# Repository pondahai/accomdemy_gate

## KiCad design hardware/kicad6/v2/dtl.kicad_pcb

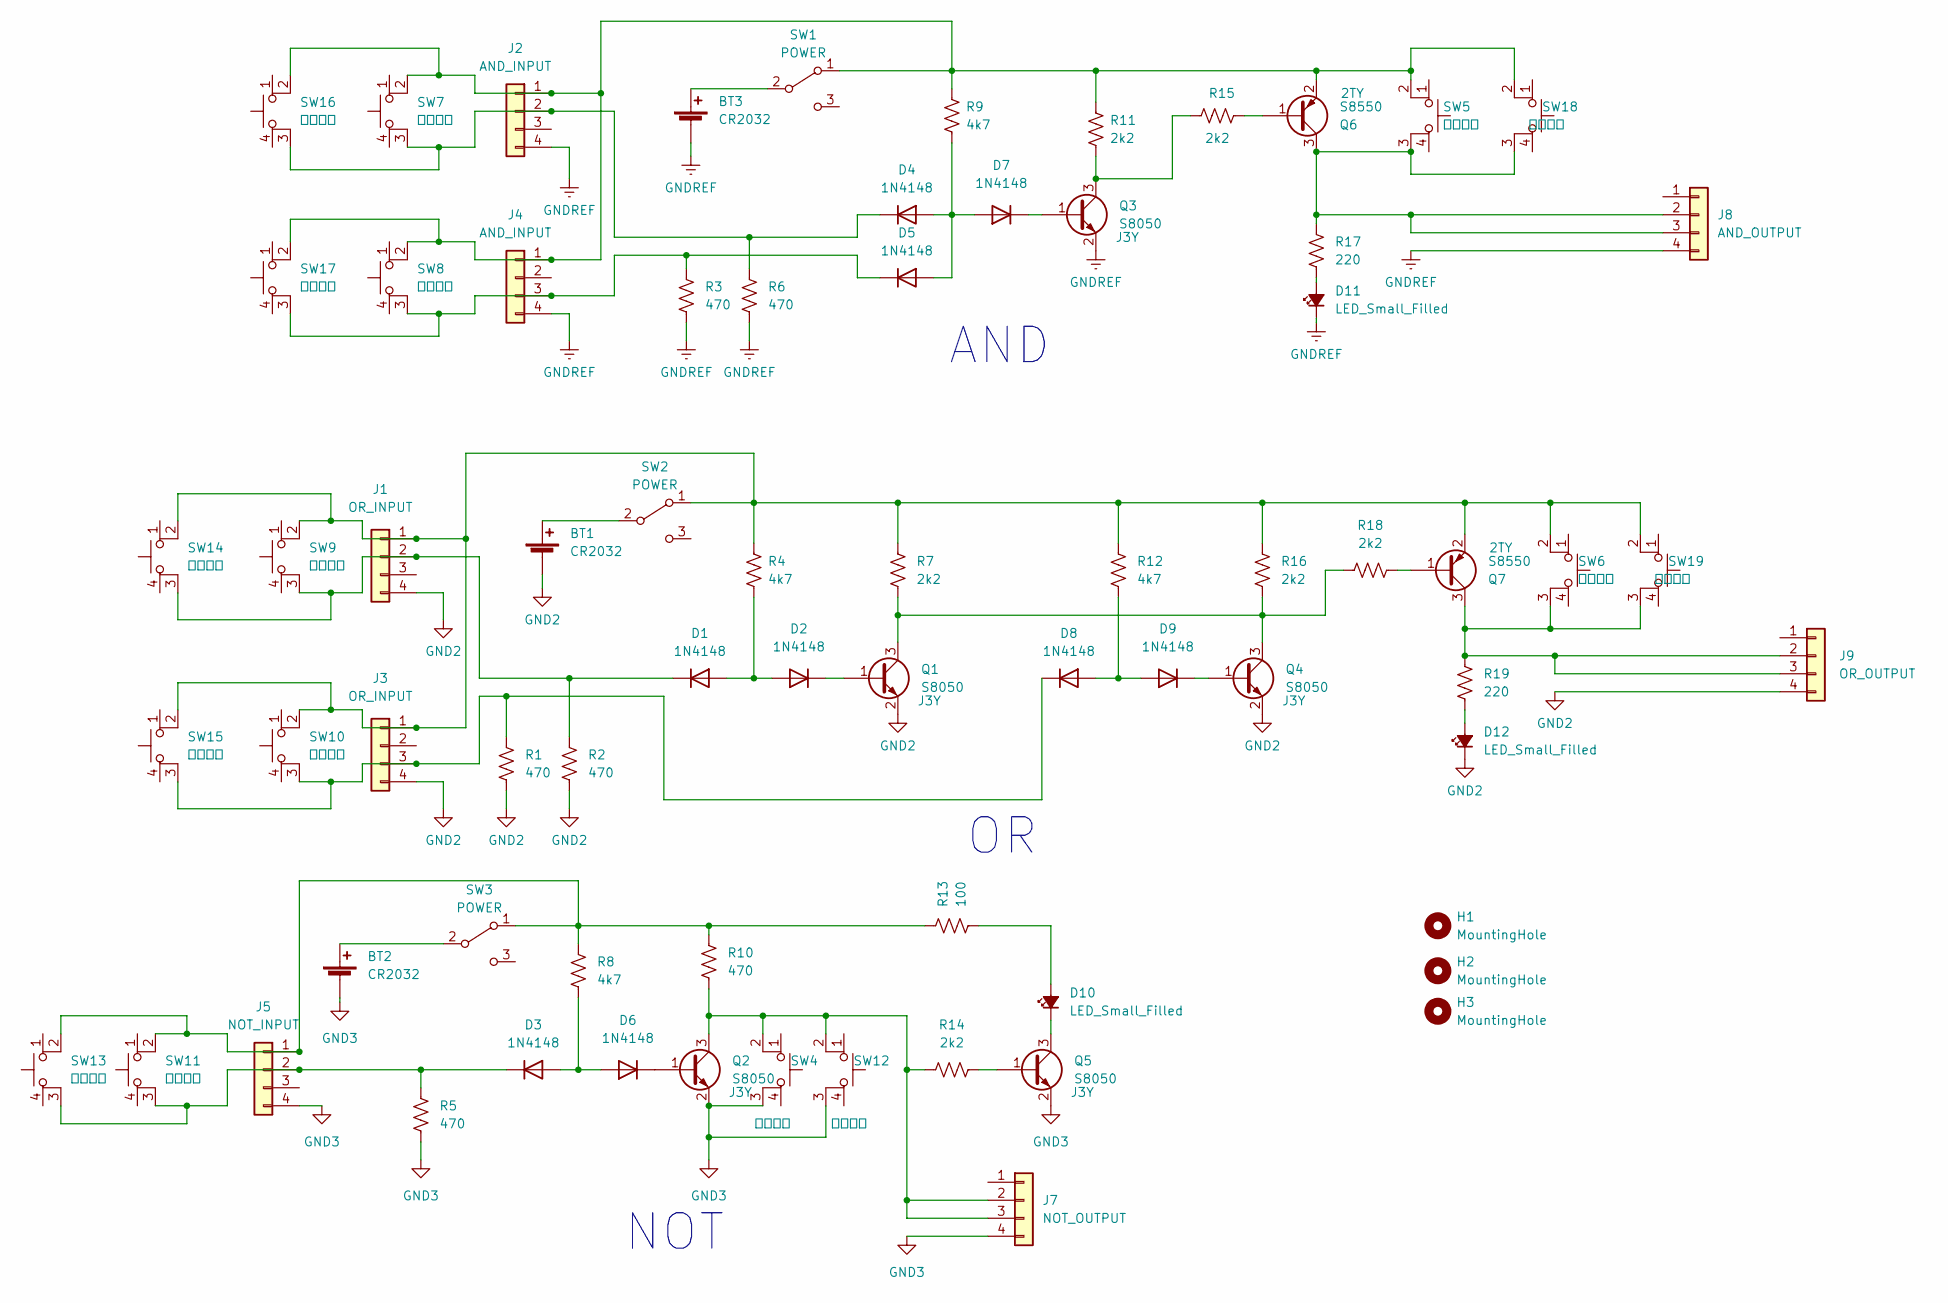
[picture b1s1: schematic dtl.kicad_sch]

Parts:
BT1, BT2, BT3: CR2032; BatteryHolder_Keystone_3002_1x2032
D1, D2, D3, D4, D5, D6, D7, D8, D9: 1N4148; D_1210_3225Metric_Pad1.42x2.65mm_HandSolder
D10, D11, D12: LED_Small_Filled; LED_D3.0mm_Clear
H1, H2, H3: MountingHole; MountingHole_2.2mm_M2
J1, J3: OR_INPUT; PinHeader_1x04_P2.54mm_Vertical
J2, J4: AND_INPUT; PinHeader_1x04_P2.54mm_Vertical
J5: NOT_INPUT; PinHeader_1x04_P2.54mm_Vertical
J7: NOT_OUTPUT; PinHeader_1x04_P2.54mm_Vertical
J8: AND_OUTPUT; PinHeader_1x04_P2.54mm_Vertical
J9: OR_OUTPUT; PinHeader_1x04_P2.54mm_Vertical
Q1, Q2, Q3, Q4, Q5: S8050; SOT-23
Q6, Q7: S8550; SOT-23
R1, R2, R3, R5, R6, R10: 470; R_0805_2012Metric_Pad1.20x1.40mm_HandSolder
R4, R8, R9, R12: 4k7; R_0805_2012Metric_Pad1.20x1.40mm_HandSolder
R7, R11, R14, R15, R16, R18: 2k2; R_0805_2012Metric_Pad1.20x1.40mm_HandSolder
R13: 100; R_0805_2012Metric_Pad1.20x1.40mm_HandSolder
R17, R19: 220; R_0805_2012Metric_Pad1.20x1.40mm_HandSolder
SW1, SW2, SW3: POWER; MK12C02
SW4, SW5, SW6: 強制輸出; skrp
SW7, SW8, SW9, SW10, SW11: 強制輸入; skrp
SW12, SW18, SW19: 強制輸出; skqg
SW13, SW14, SW15, SW16, SW17: 強制輸入; skqg

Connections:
GND2: BT1.2 (-), D12.1 (K), J1.4, J3.4, J9.4, Q1.2 (E), Q4.2 (E), R1.2, R2.2
GND3: BT2.2 (-), J5.4, J7.4, Q2.2 (E), Q5.2 (E), R5.2, SW4.3 (K), SW12.3 (K)
GNDREF: BT3.2 (-), D11.1 (K), J2.4, J4.4, J8.4, Q3.2 (E), R3.2, R6.2
unnamed: BT1.1 (+), SW2.2 (B)
unnamed: BT2.1 (+), SW3.2 (B)
unnamed: BT3.1 (+), SW1.2 (B)
unnamed: D1.1 (K), J1.2, R2.1, SW9.3 (K), SW14.3 (K)
unnamed: D1.2 (A), D2.2 (A), R4.2
unnamed: D2.1 (K), Q1.1 (B)
unnamed: D3.1 (K), J5.2, R5.1, SW11.3 (K), SW13.3 (K)
unnamed: D3.2 (A), D6.2 (A), R8.2
unnamed: D4.1 (K), J2.2, R6.1, SW7.3 (K), SW16.3 (K)
unnamed: D4.2 (A), D5.2 (A), D7.2 (A), R9.2
unnamed: D5.1 (K), J4.3, R3.1, SW8.3 (K), SW17.3 (K)
unnamed: D6.1 (K), Q2.1 (B)
unnamed: D7.1 (K), Q3.1 (B)
unnamed: D8.1 (K), J3.3, R1.1, SW10.3 (K), SW15.3 (K)
unnamed: D8.2 (A), D9.2 (A), R12.2
unnamed: D9.1 (K), Q4.1 (B)
unnamed: D10.1 (K), Q5.3 (C)
unnamed: D10.2 (A), R13.2
unnamed: D11.2 (A), R17.2
unnamed: D12.2 (A), R19.2
unnamed: J7.2, J7.3, Q2.3 (C), R10.2, R14.1, SW4.2, SW12.2
unnamed: J8.2, J8.3, Q6.3 (C), R17.1, SW5.3 (K), SW18.3 (K)
unnamed: J9.2, J9.3, Q7.3 (C), R19.1, SW6.3 (K), SW19.3 (K)
unnamed: Q1.3 (C), Q4.3 (C), R7.2, R16.2, R18.1
unnamed: Q3.3 (C), R11.1, R15.1
unnamed: Q5.1 (B), R14.2
unnamed: Q6.1 (B), R15.2
unnamed: J2.1, J4.1, Q6.2 (E), R9.1, R11.2, SW1.1 (A), SW5.2, SW7.2, SW8.2, SW16.2, SW17.2, SW18.2
unnamed: Q7.1 (B), R18.2
unnamed: J1.1, J3.1, Q7.2 (E), R4.1, R7.1, R12.1, R16.1, SW2.1 (A), SW6.2, SW9.2, SW10.2, SW14.2, SW15.2, SW19.2
unnamed: J5.1, R8.1, R10.1, R13.1, SW3.1 (A), SW11.2, SW13.2

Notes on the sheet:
NOT
AND

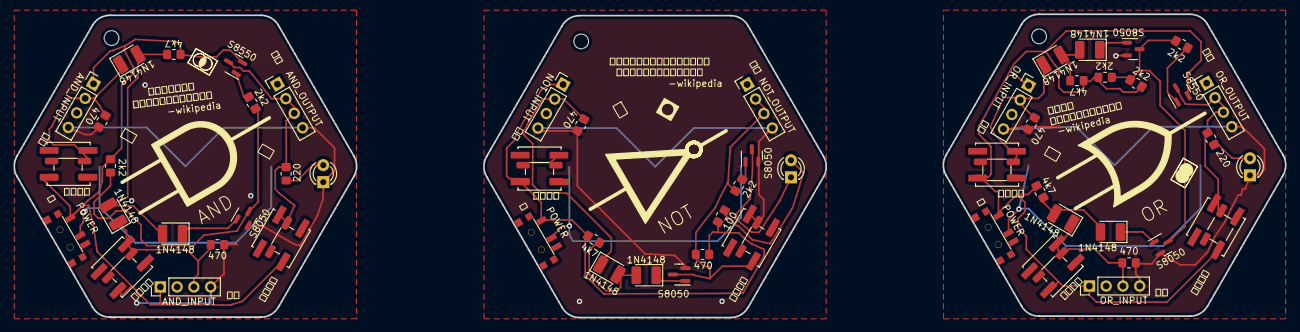
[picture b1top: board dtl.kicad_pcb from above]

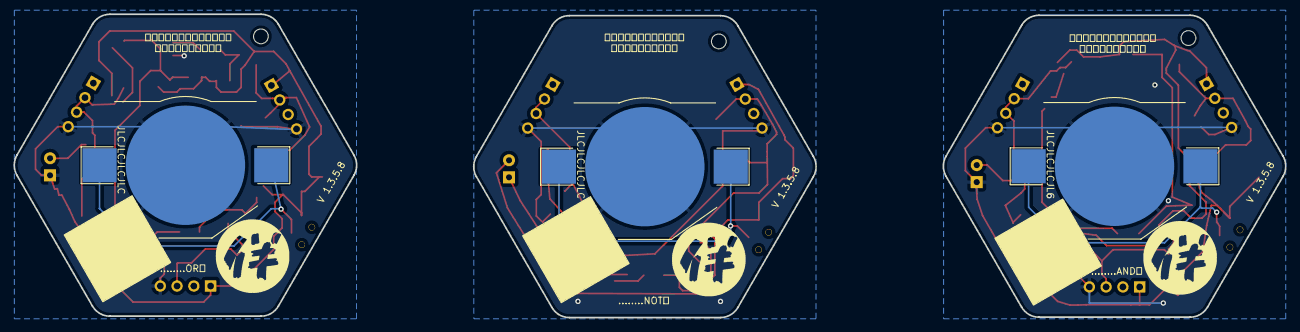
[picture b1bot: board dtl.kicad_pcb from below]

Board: 2 copper layers, 189.5 x 45.2 mm, 71 parts (3 on the bottom side), 34 nets.
